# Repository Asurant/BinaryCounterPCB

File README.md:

# BinaryCounterPCB

I'm made a binary counter that uses LEDs to show 1s and 0s and can count up to 255. It was made with the help of a CD4040 IC.
## Features
This board has:
- Decimal Values Of Each Binary LED
- An Addition Button For Adding 1 To The Binary
- A Rest Button To Reset The LEDs
## Schematic

## PCB

## BOM

| Designator | Footprint | Quantity | Value |
| :--- | :--- | :--- | :--- |
| D1, D2, D3, D4, D5, D6, D7, D8 | 	LED_D5.0mm | 8 | LED |
| J1 | USB_A_Molex_67643_Horizontal | 1 | USB_A |
| R1, R2 | R_Axial_DIN0204_L3.6mm_D1.6mm_P7.62mm_Horizontal | 2 | 1k |
| R3 | R_Axial_DIN0204_L3.6mm_D1.6mm_P7.62mm_Horizontal | 1 | 470 |
| SW1, SW2 | SW_PUSH_6mm | 2 | SW_Push |
| U1 | DIP-16_W7.62mm | 1 | 4040 |

## Assembly
Overall the components are interchangable as long as you keep them between the same type of components. Put the USB A where is says J1, the CD4040 where it says U1, the switches on SW1 and SW2 (They are the same kind so don't worry about which one you're using), LEDs can be put in whatever order as long as they are put in properly with the positive and negatives going where they should go. However you need to be careful with the resistors. While R1 and R2 are 1k, R3 is 470. So put your 1k resistors to the locations to the right of the CD4040 and put your 470 resistor below the USB A port.

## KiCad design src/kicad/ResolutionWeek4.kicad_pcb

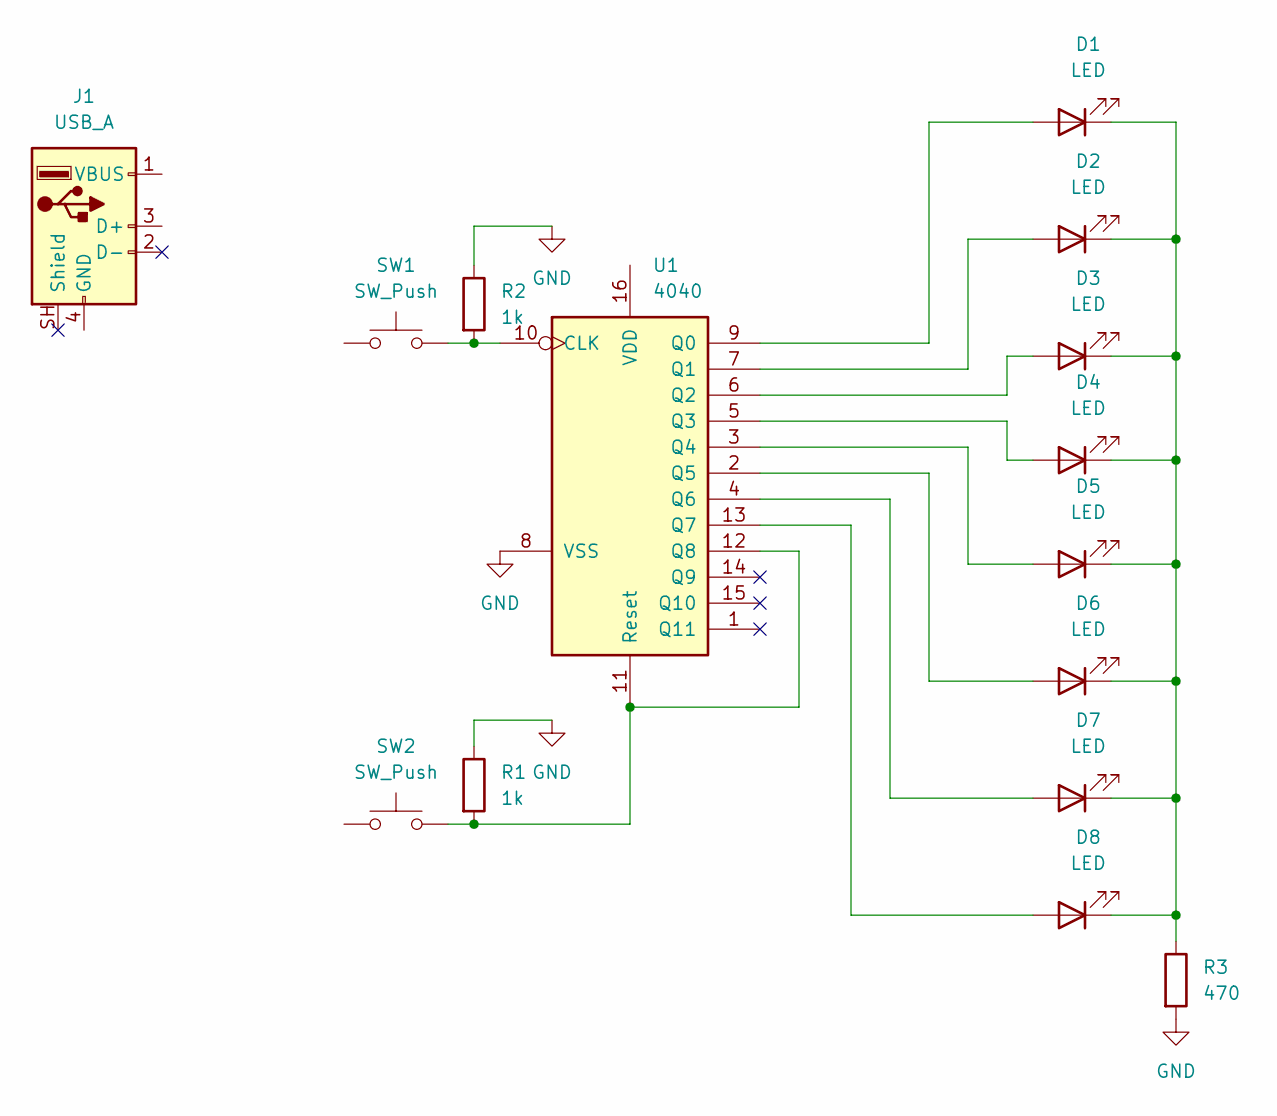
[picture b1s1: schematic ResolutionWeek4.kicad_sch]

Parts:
D1, D2, D3, D4, D5, D6, D7, D8: LED
J1: USB_A
R1, R2: 1k
R3: 470
SW1, SW2: SW_Push
U1: 4040

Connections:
GND: J1.4 (GND), R1.1, R2.1, R3.2, U1.8 (VSS)
unnamed: D1.2 (A), U1.9 (Q0)
unnamed: D1.1 (K), D2.1 (K), D3.1 (K), D4.1 (K), D5.1 (K), D6.1 (K), D7.1 (K), D8.1 (K), R3.1
unnamed: D2.2 (A), U1.7 (Q1)
unnamed: D3.2 (A), U1.6 (Q2)
unnamed: D4.2 (A), U1.5 (Q3)
unnamed: D5.2 (A), U1.3 (Q4)
unnamed: D6.2 (A), U1.2 (Q5)
unnamed: D7.2 (A), U1.4 (Q6)
unnamed: D8.2 (A), U1.13 (Q7)
unnamed: R2.2, SW1.2, U1.10 (CLK)
unnamed: R1.2, SW2.2, U1.11 (Reset), U1.12 (Q8)
VCC: J1.1 (VBUS), SW1.1, SW2.1, U1.16 (VDD)

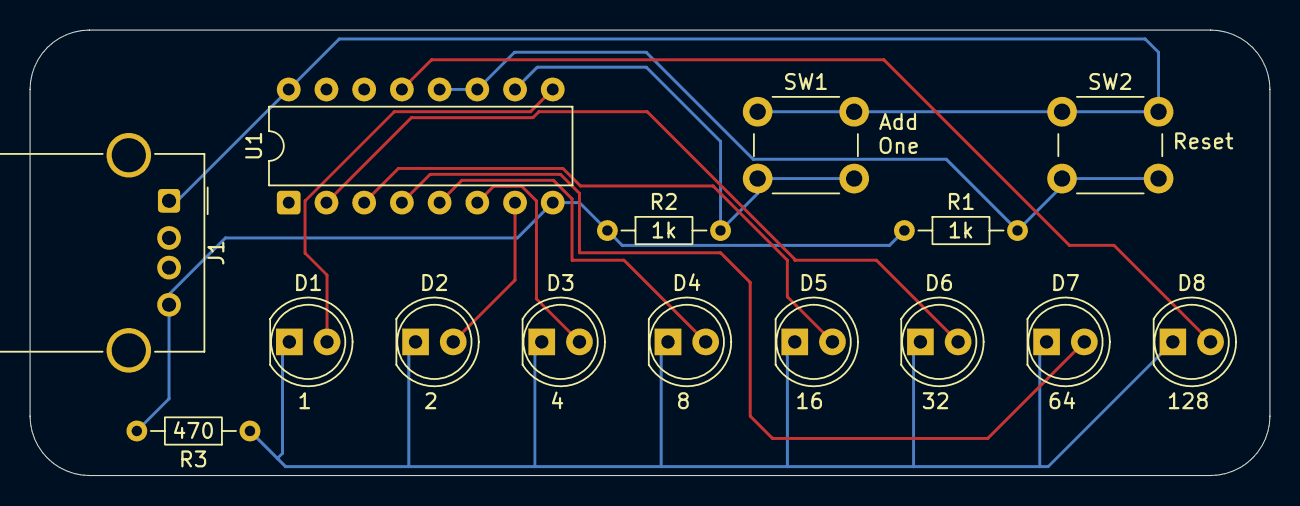
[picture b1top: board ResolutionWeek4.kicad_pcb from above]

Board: 2 copper layers, 83.5 x 30.0 mm, 15 parts (0 on the bottom side), 13 nets.

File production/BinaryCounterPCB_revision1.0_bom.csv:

Designator,Footprint,Quantity,Value,LCSC Part #
"D1, D2, D3, D4, D5, D6, D7, D8",LED_D5.0mm,8,LED,
J1,USB_A_Molex_67643_Horizontal,1,USB_A,
"R1, R2",R_Axial_DIN0204_L3.6mm_D1.6mm_P7.62mm_Horizontal,2,1k,
R3,R_Axial_DIN0204_L3.6mm_D1.6mm_P7.62mm_Horizontal,1,470,
"SW1, SW2",SW_PUSH_6mm,2,SW_Push,
U1,DIP-16_W7.62mm,1,4040,

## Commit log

2026-04-18 Create temp
2026-04-18 Fixing Mistake
    I accidentally had uploaded the old version of my schematic. Fixing it by adding the new one (if you wish to check I have a screenshot of the new version in attachments that was made before I uploade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
